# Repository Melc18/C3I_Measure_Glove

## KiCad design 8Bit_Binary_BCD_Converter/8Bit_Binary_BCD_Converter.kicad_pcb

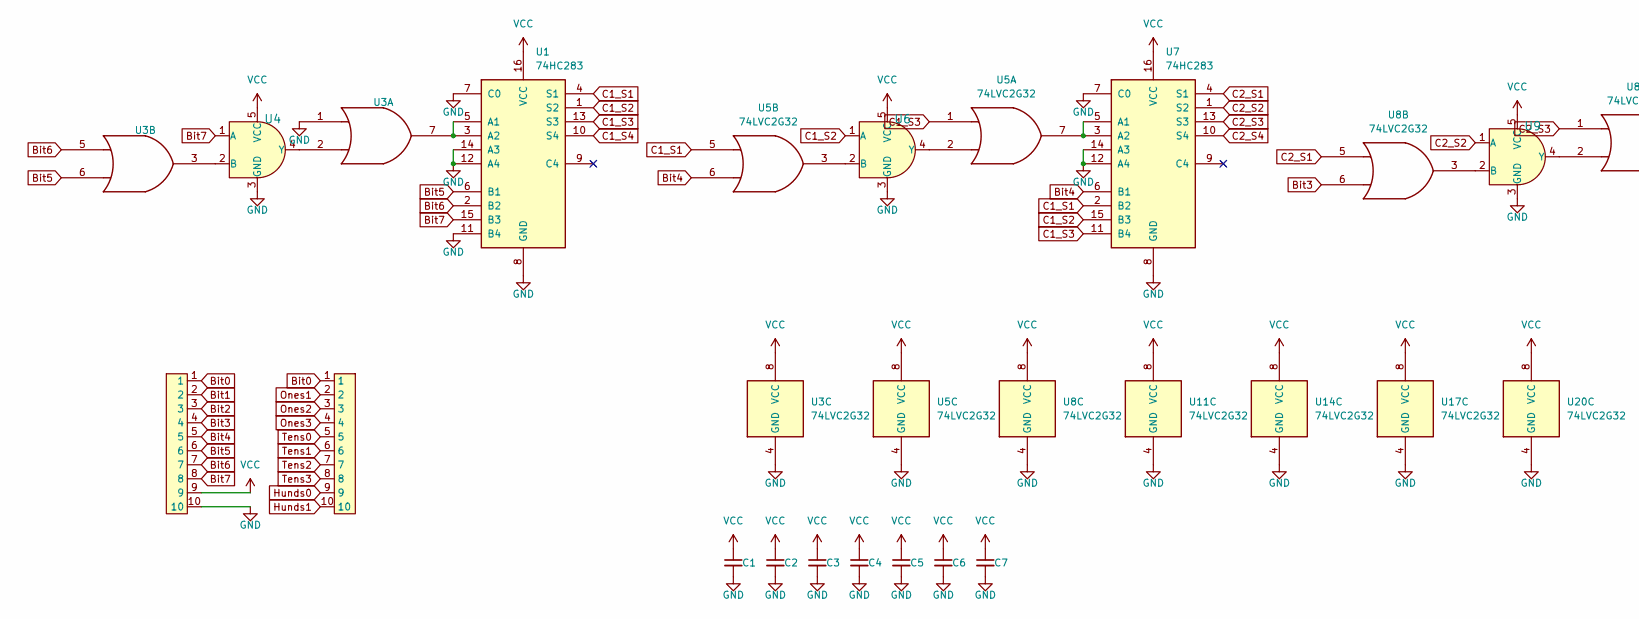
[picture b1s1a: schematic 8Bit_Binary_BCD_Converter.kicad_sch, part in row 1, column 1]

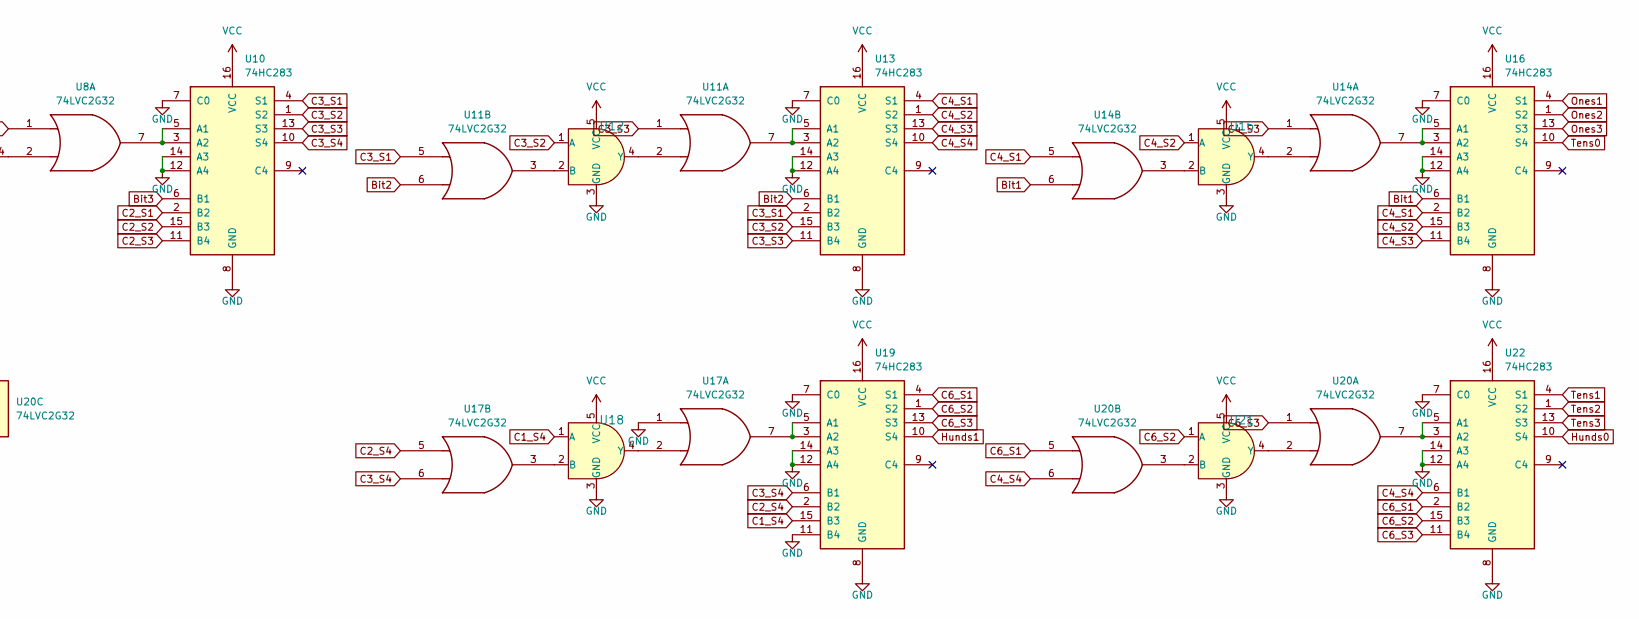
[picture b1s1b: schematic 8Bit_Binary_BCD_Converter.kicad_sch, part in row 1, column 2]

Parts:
C1, C2, C3, C4, C5, C6, C7: C_Small; C_0603_1608Metric_Pad1.08x0.95mm_HandSolder
U1, U7, U10, U13, U16, U19, U22: 74HC283; CD74HC283M96-M
U2, U23: Header 10P 2.54mm
U3, U5, U8, U11, U14, U17, U20: 74LVC2G32; DCU8-L
U4, U6, U9, U12, U15, U18, U21: SN74LVC1G08DCKR; DCK5; MPN SN74LVC1G08DCKR; Digi-Key_PN 296-11602-1-ND

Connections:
Bit0: U2.1, U23.1
Bit1: U2.2, U14.6, U16.6 (B1)
Bit2: U2.3, U11.6, U13.6 (B1)
Bit3: U2.4, U8.6, U10.6 (B1)
Bit4: U2.5, U5.6, U7.6 (B1)
Bit5: U1.6 (B1), U2.6, U3.6
Bit6: U1.2 (B2), U2.7, U3.5
Bit7: U1.15 (B3), U2.8, U4.1 (A)
C1_S1: U1.4 (S1), U5.5, U7.2 (B2)
C1_S2: U1.1 (S2), U6.1 (A), U7.15 (B3)
C1_S3: U1.13 (S3), U5.1, U7.11 (B4)
C1_S4: U1.10 (S4), U18.1 (A), U19.15 (B3)
C2_S1: U7.4 (S1), U8.5, U10.2 (B2)
C2_S2: U7.1 (S2), U9.1 (A), U10.15 (B3)
C2_S3: U7.13 (S3), U8.1, U10.11 (B4)
C2_S4: U7.10 (S4), U17.5, U19.2 (B2)
C3_S1: U10.4 (S1), U11.5, U13.2 (B2)
C3_S2: U10.1 (S2), U12.1 (A), U13.15 (B3)
C3_S3: U10.13 (S3), U11.1, U13.11 (B4)
C3_S4: U10.10 (S4), U17.6, U19.6 (B1)
C4_S1: U13.4 (S1), U14.5, U16.2 (B2)
C4_S2: U13.1 (S2), U15.1 (A), U16.15 (B3)
C4_S3: U13.13 (S3), U14.1, U16.11 (B4)
C4_S4: U13.10 (S4), U20.6, U22.6 (B1)
C6_S1: U19.4 (S1), U20.5, U22.2 (B2)
C6_S2: U19.1 (S2), U21.1 (A), U22.15 (B3)
C6_S3: U19.13 (S3), U20.1, U22.11 (B4)
GND: C1.2, C2.2, C3.2, C4.2, C5.2, C6.2, C7.2, U1.7 (C0), U1.8 (GND), U1.11 (B4), U1.12 (A4), U1.14 (A3), U2.10, U3.1, U3.4 (GND), U4.3 (GND), U5.4 (GND), U6.3 (GND), U7.7 (C0), U7.8 (GND), U7.12 (A4), U7.14 (A3), U8.4 (GND), U9.3 (GND), U10.7 (C0), U10.8 (GND), U10.12 (A4), U10.14 (A3), U11.4 (GND), U12.3 (GND), U13.7 (C0), U13.8 (GND), U13.12 (A4), U13.14 (A3), U14.4 (GND), U15.3 (GND), U16.7 (C0), U16.8 (GND), U16.12 (A4), U16.14 (A3), U17.1, U17.4 (GND), U18.3 (GND), U19.7 (C0), U19.8 (GND), U19.11 (B4), U19.12 (A4), U19.14 (A3), U20.4 (GND), U21.3 (GND), U22.7 (C0), U22.8 (GND), U22.12 (A4), U22.14 (A3)
Hunds0: U22.10 (S4), U23.9
Hunds1: U19.10 (S4), U23.10
unnamed: U1.3 (A2), U1.5 (A1), U3.7
unnamed: U3.3, U4.2 (B)
unnamed: U3.2, U4.4 (Y)
unnamed: U5.3, U6.2 (B)
unnamed: U5.2, U6.4 (Y)
unnamed: U5.7, U7.3 (A2), U7.5 (A1)
unnamed: U8.3, U9.2 (B)
unnamed: U8.2, U9.4 (Y)
unnamed: U8.7, U10.3 (A2), U10.5 (A1)
unnamed: U11.3, U12.2 (B)
unnamed: U11.2, U12.4 (Y)
unnamed: U11.7, U13.3 (A2), U13.5 (A1)
unnamed: U14.3, U15.2 (B)
unnamed: U14.2, U15.4 (Y)
unnamed: U14.7, U16.3 (A2), U16.5 (A1)
unnamed: U17.3, U18.2 (B)
unnamed: U17.2, U18.4 (Y)
unnamed: U17.7, U19.3 (A2), U19.5 (A1)
unnamed: U20.3, U21.2 (B)
unnamed: U20.2, U21.4 (Y)
unnamed: U20.7, U22.3 (A2), U22.5 (A1)
Ones1: U16.4 (S1), U23.2
Ones2: U16.1 (S2), U23.3
Ones3: U16.13 (S3), U23.4
Tens0: U16.10 (S4), U23.5
Tens1: U22.4 (S1), U23.6
Tens2: U22.1 (S2), U23.7
Tens3: U22.13 (S3), U23.8
VCC: C1.1, C2.1, C3.1, C4.1, C5.1, C6.1, C7.1, U1.16 (VCC), U2.9, U3.8 (VCC), U4.5 (VCC), U5.8 (VCC), U6.5 (VCC), U7.16 (VCC), U8.8 (VCC), U9.5 (VCC), U10.16 (VCC), U11.8 (VCC), U12.5 (VCC), U13.16 (VCC), U14.8 (VCC), U15.5 (VCC), U16.16 (VCC), U17.8 (VCC), U18.5 (VCC), U19.16 (VCC), U20.8 (VCC), U21.5 (VCC), U22.16 (VCC)

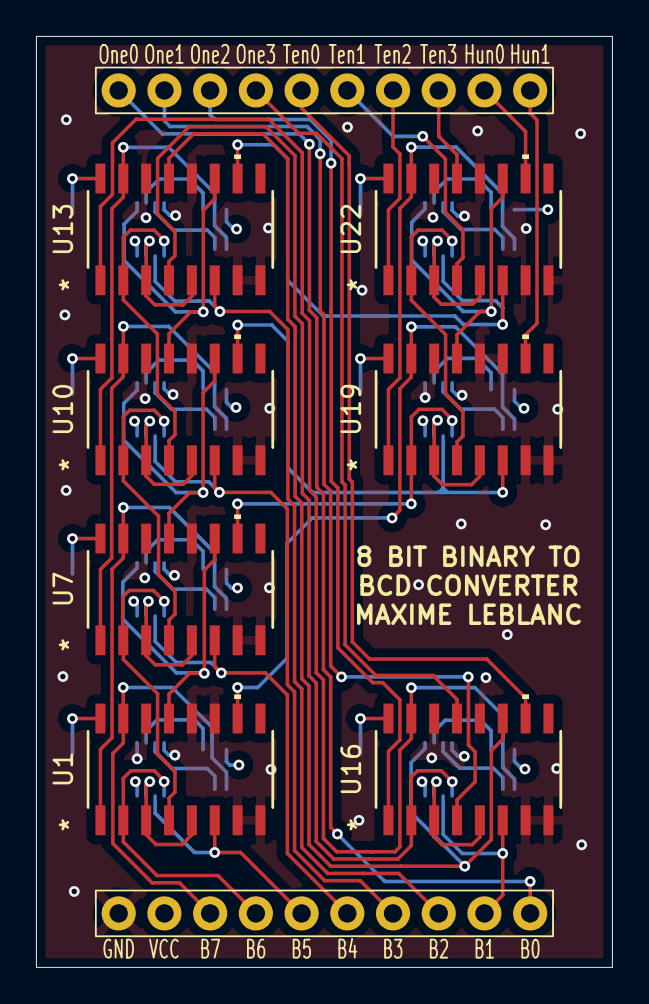
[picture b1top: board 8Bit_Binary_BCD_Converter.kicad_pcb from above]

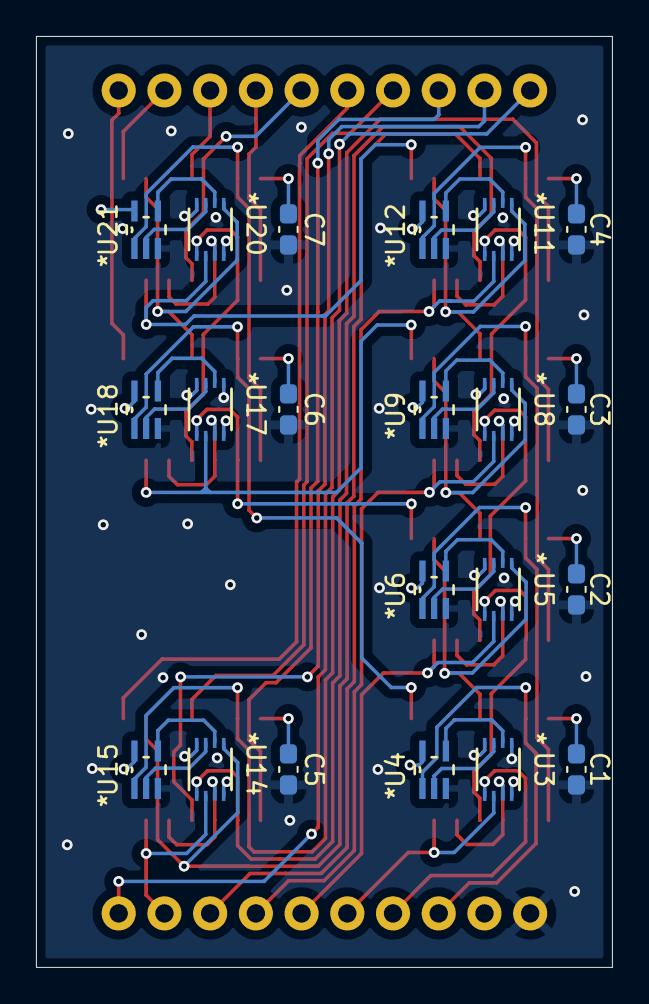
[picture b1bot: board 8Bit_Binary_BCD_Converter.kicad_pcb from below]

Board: 4 copper layers, 32.0 x 51.7 mm, 30 parts (21 on the bottom side), 59 nets.

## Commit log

2026-03-20 Kicad gitignore
2026-03-20 Init commit
2026-03-25 Master_Glove project
2026-03-29 Excel calculation and creation of division in project
    Small push with All pages created with naming following how tasks were seperated before placing components
2026-04-01 Circuit Log+Sub fait
2026-04-01 Edit formula with new info
2026-04-02 Switch+555+SR
    work in progress
2026-04-03 Finished BCD Converter + BOM + Gerber Files
2026-04-04 Ultrasound transceiver in BOM
2026-04-05 work on discharge
2026-04-06 Working on emitter Circuit
2026-04-11 Conversion + Display Schematic. Missing forced ground on ADC booth
2026-04-22 Circuit ready for review
    Added connection to sensor with push-pull output circuit and changed resistances to be U.S.A. format
2026-04-22 Simplifications and modifications following Myriam Recommendation
    Circuit will be validated this weekend by Myriam
2026-05-06 Power
2026-05-06 Lock
2026-05-07 Modifications according to reccomendation
    Changed Vcc to +5V
    Subbed MIC1551 to MIC 1553
    Added debounce on button
    Fixed other small bugs
2026-05-07 fix bug
    added comment for resistor in series for sensor not needed since already built in NPN
2026-05-12 Adding footprints
2026-05-13 BCD converter fix
2026-05-25 ADC init circuit draft
2026-05-26 added footprints
2026-05-26 closed kicad
2026-05-26 fixed potentiometer
